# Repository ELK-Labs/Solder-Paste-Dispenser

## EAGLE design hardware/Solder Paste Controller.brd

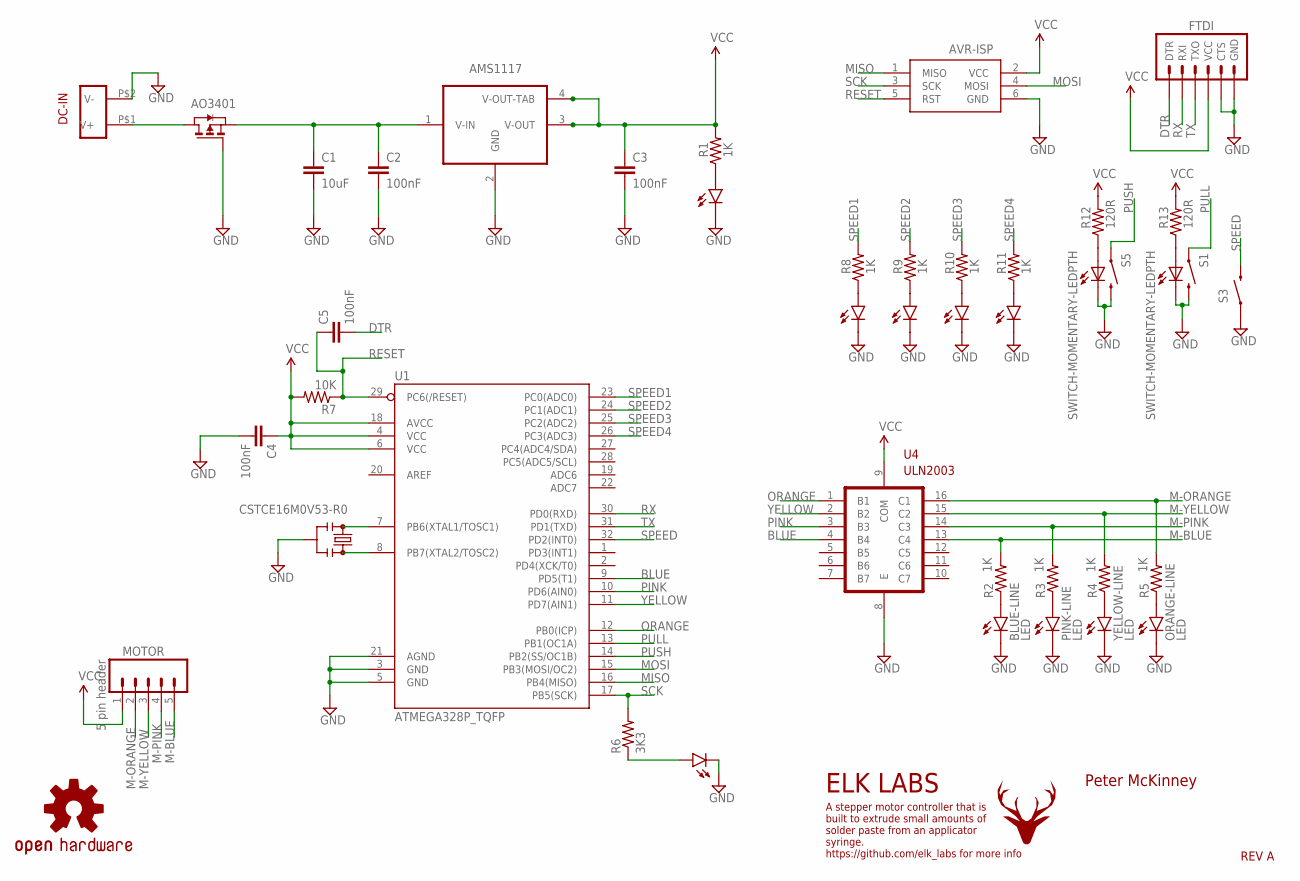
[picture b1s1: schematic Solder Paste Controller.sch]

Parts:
AVR-ISP: AVRISP-6; AVRISP
BLUE-LINE: LED; 0805-LED
C1: 10uF; 0805
C2, C3, C4, C5: 100nF; 0805
CRYSTAL: CSTCE16M0V53-R0; CSTCE_V
DC-IN: red black twister wire; POWER_CONNECTOR_WITH_RELIEF
FTDI: 6 pin header; 1X06
HEARTBEAT: LED; 0805-LED
LOGO1: OSHW-LOGOS; OSHW-LOGO-S
MOTOR: 5 pin header; 1X05
ORANGE-LINE: LED; 0805-LED
PINK-LINE: LED; 0805-LED
PWRLED: LED; 0805-LED
R1, R2, R3, R4, R5, R8, R9, R10, R11: 1K; 0805
R6: 3K3; 0805
R7: 10K; 0805
R12, R13: 120R; 0805
S1, S5: SWITCH-MOMENTARY-LEDPTH; TACTILE-PTH-LED-12MM
S3: SWITCH-MOMENTARY-2SMD-1101NE; TACTILE-SWITCH-1101NE
SPEED1LED, SPEED2LED, SPEED3LED, SPEED4LED: LED; 0805-LED
U1: ATMEGA328P_TQFP; TQFP32-08
U2: AMS1117; SOT-223
U3: AO3401; SOT-23
U4: ULN2003; SOP-16
U$1: ELK-LOGO
YELLOW-LINE: LED; 0805-LED

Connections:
BLUE: U1.9 (PD5(T1)), U4.4 (B4)
DTR: C5.2, FTDI.1 (DTR)
GND: AVR-ISP.6 (GND), BLUE-LINE.C, C1.2, C2.2, C3.2, C4.2, CRYSTAL.GND, DC-IN.P$2 (V-), FTDI.5 (CTS), FTDI.6 (GND), HEARTBEAT.C, ORANGE-LINE.C, PINK-LINE.C, PWRLED.C, S1.2, S1.C, S3.1, S5.2, S5.C, SPEED1LED.C, SPEED2LED.C, SPEED3LED.C, SPEED4LED.C, U1.3 (GND), U1.5 (GND), U1.21 (AGND), U2.2 (GND), U3.1 (G), U4.8 (E), YELLOW-LINE.C
M-BLUE: MOTOR.5, R2.2, U4.13 (C4)
M-ORANGE: MOTOR.2, R5.2, U4.16 (C1)
M-PINK: MOTOR.4, R3.2, U4.14 (C3)
M-YELLOW: MOTOR.3, R4.2, U4.15 (C2)
MISO: AVR-ISP.1 (MISO), U1.16 (PB4(MISO))
MOSI: AVR-ISP.4 (MOSI), U1.15 (PB3(MOSI/OC2))
unnamed: C1.1, C2.1, U2.1 (V-IN), U3.2 (S)
unnamed: PWRLED.A, R1.1
unnamed: CRYSTAL.1, U1.7 (PB6(XTAL1/TOSC1))
unnamed: CRYSTAL.3, U1.8 (PB7(XTAL2/TOSC2))
unnamed: DC-IN.P$1 (V+), U3.3 (D)
unnamed: BLUE-LINE.A, R2.1
unnamed: PINK-LINE.A, R3.1
unnamed: R4.1, YELLOW-LINE.A
unnamed: ORANGE-LINE.A, R5.1
unnamed: R12.1, S5.A
unnamed: R13.1, S1.A
unnamed: HEARTBEAT.A, R6.1
unnamed: R8.1, SPEED1LED.A
unnamed: R9.1, SPEED2LED.A
unnamed: R10.1, SPEED3LED.A
unnamed: R11.1, SPEED4LED.A
ORANGE: U1.12 (PB0(ICP)), U4.1 (B1)
PINK: U1.10 (PD6(AIN0)), U4.3 (B3)
PULL: S1.4 (1), U1.13 (PB1(OC1A))
PUSH: S5.4 (1), U1.14 (PB2(SS/OC1B))
RESET: AVR-ISP.5 (RST), C5.1, R7.1, U1.29 (PC6(/RESET))
RX: FTDI.2 (RXI), U1.30 (PD0(RXD))
SCK: AVR-ISP.3 (SCK), R6.2, U1.17 (PB5(SCK))
SPEED: S3.2, U1.32 (PD2(INT0))
SPEED1: R8.2, U1.23 (PC0(ADC0))
SPEED2: R9.2, U1.24 (PC1(ADC1))
SPEED3: R10.2, U1.25 (PC2(ADC2))
SPEED4: R11.2, U1.26 (PC3(ADC3))
TX: FTDI.3 (TXO), U1.31 (PD1(TXD))
VCC: AVR-ISP.2 (VCC), C3.1, C4.1, FTDI.4 (VCC), MOTOR.1, R1.2, R7.2, R12.2, R13.2, U1.4 (VCC), U1.6 (VCC), U1.18 (AVCC), U2.3 (V-OUT), U2.4 (V-OUT-TAB), U4.9 (COM)
YELLOW: U1.11 (PD7(AIN1)), U4.2 (B2)

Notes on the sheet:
Peter McKinney
ELK LABS
A stepper motor controller that is built to extrude small amounts of solder paste from an applicator syringe. https://github.com/elk_labs for more info
REV A

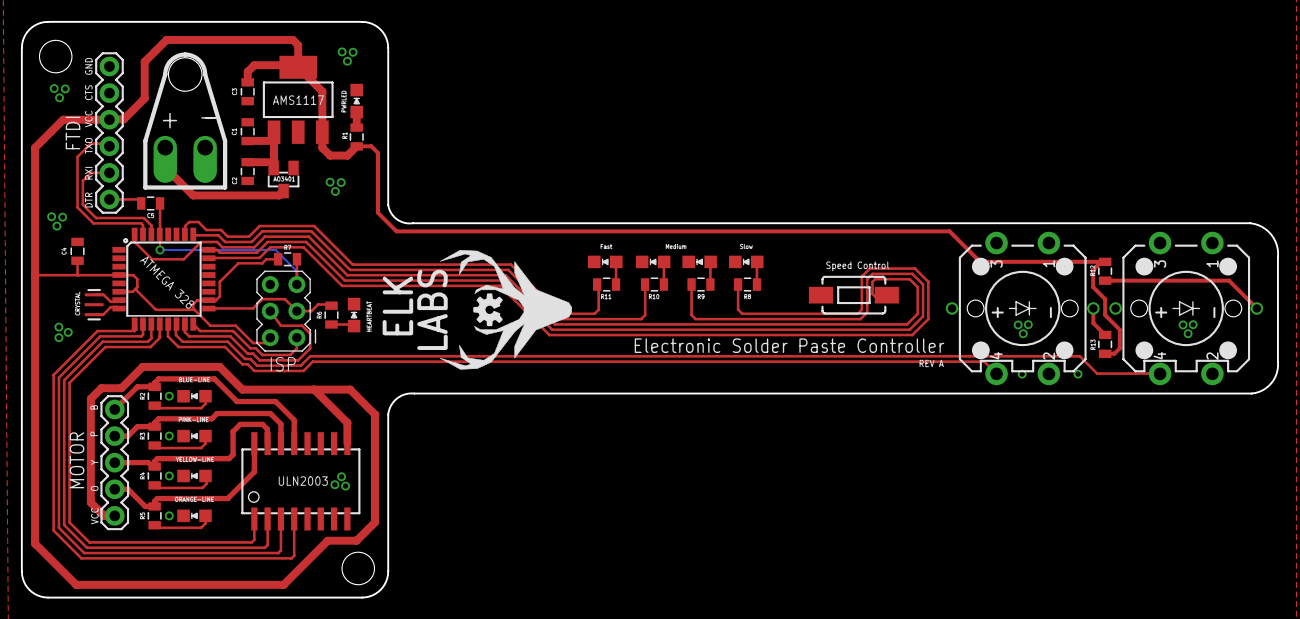
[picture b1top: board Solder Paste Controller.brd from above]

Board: 2 copper layers, 120.0 x 55.0 mm, 42 parts (0 on the bottom side), 40 nets.

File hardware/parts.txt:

Partlist

Exported from Solder Paste Controller.sch at 20/03/2016 17:41

EAGLE Version 7.5.0 Copyright (c) 1988-2015 CadSoft

Assembly variant: 

Part        Value                        Device                       Package                     Library                    Sheet

AVR-ISP     AVRISP-6                     AVRISP-6                     AVRISP                      adafruit                   1
BLUE-LINE   LED                          LED                          0805-LED                    ELK LABS                   1
C1          10uF                         1UF-25V-10%(0805)            0805                        SparkFun-Capacitors        1
C2          100nF                        1UF-25V-10%(0805)            0805                        SparkFun-Capacitors        1
C3          100nF                        1UF-25V-10%(0805)            0805                        SparkFun-Capacitors        1
C4          100nF                        1UF-25V-10%(0805)            0805                        SparkFun-Capacitors        1
C5          100nF                        1UF-25V-10%(0805)            0805                        SparkFun-Capacitors        1
CRYSTAL     CSTCE16M0V53-R0              CSTCE16M0V53-R0              CSTCE_V                     ELK LABS                   1
DC-IN       POWER-IN-WITH-RELIEF         POWER-IN-WITH-RELIEF         POWER_CONNECTOR_WITH_RELIEF ELK LABS                   1
FTDI                                     ARDUINO_SERIAL_PROGRAMPTH    1X06                        SparkFun-Connectors        1
HEARTBEAT   LED                          LED                          0805-LED                    ELK LABS                   1
MOTOR                                    M05PTH                       1X05                        SparkFun-Connectors        1
ORANGE-LINE LED                          LED                          0805-LED                    ELK LABS                   1
PINK-LINE   LED                          LED                          0805-LED                    ELK LABS                   1
PWRLED      LED                          LED                          0805-LED                    ELK LABS                   1
R1          1K                           RESISTOR0805-RES             0805                        SparkFun-Passives          1
R2          1K                           RESISTOR0805-RES             0805                        SparkFun-Passives          1
R3          1K                           RESISTOR0805-RES             0805                        SparkFun-Passives          1
R4          1K                           RESISTOR0805-RES             0805                        SparkFun-Passives          1
R5          1K                           RESISTOR0805-RES             0805                        SparkFun-Passives          1
R6          3K3                          RESISTOR0805-RES             0805                        SparkFun-Passives          1
R7          10K                          RESISTOR0805-RES             0805                        SparkFun-Passives          1
R8          1K                           RESISTOR0805-RES             0805                        SparkFun-Passives          1
R9          1K                           RESISTOR0805-RES             0805                        SparkFun-Passives          1
R10         1K                           RESISTOR0805-RES             0805                        SparkFun-Passives          1
R11         1K                           RESISTOR0805-RES             0805                        SparkFun-Passives          1
R12         120R                         RESISTOR0805-RES             0805                        SparkFun-Passives          1
R13         120R                         RESISTOR0805-RES             0805                        SparkFun-Passives          1
S1          SWITCH-MOMENTARY-LEDPTH      SWITCH-MOMENTARY-LEDPTH      TACTILE-PTH-LED-12MM        SparkFun-Electromechanical 1
S3          SWITCH-MOMENTARY-2SMD-1101NE SWITCH-MOMENTARY-2SMD-1101NE TACTILE-SWITCH-1101NE       SparkFun-Electromechanical 1
S5          SWITCH-MOMENTARY-LEDPTH      SWITCH-MOMENTARY-LEDPTH      TACTILE-PTH-LED-12MM        SparkFun-Electromechanical 1
SPEED1LED   LED                          LED                          0805-LED                    ELK LABS                   1
SPEED2LED   LED                          LED                          0805-LED                    ELK LABS                   1
SPEED3LED   LED                          LED                          0805-LED                    ELK LABS                   1
SPEED4LED   LED                          LED                          0805-LED                    ELK LABS                   1
U1          ATMEGA328P_TQFP              ATMEGA328P_TQFP              TQFP32-08                   SparkFun-DigitalIC         1
U2          AMS1117                      AMS1117                      SOT-223                     ELK LABS                   1
U3          AO3401                       AO3401                       SOT-23                      ELK LABS                   1
U4          ULN2003                      ULN2003                      SOP-16                      ELK LABS                   1
YELLOW-LINE LED                          LED                          0805-LED                    ELK LABS                   1

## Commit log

2016-03-20 initial hardware commit
2016-03-20 updating parts.txt
2016-03-30 added mounting holes

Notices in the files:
parts and their libraries:
SparkFun-Capacitors: Licensing: Creative Commons ShareAlike 4.0 International - https://creativecommons.org/licenses/by-sa/4.0
